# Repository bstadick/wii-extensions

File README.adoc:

= Wii Extension Controller Library for Arduino =

This project is an unofficial Arduino library for Wii extension controllers.

Use this library to receive data from your Wii extension controllers.

See examples folder for example usage with various Wii extension controllers.

See circuit folder for circuit board schematic to connect a Wii extension controller to an Arduino Nano.

See more information on the [Wii Brew Wiki](http://wiibrew.org/wiki/Wiimote/Extension_Controllers).

Project is based off of work by [Gabriel Bianconi](http://www.gabrielbianconi.com/)

Wii is a trademark of [Nintendo](https://www.nintendo.com/). The author of this library does not claim any ownership or association with Nintendo or their affiliates.

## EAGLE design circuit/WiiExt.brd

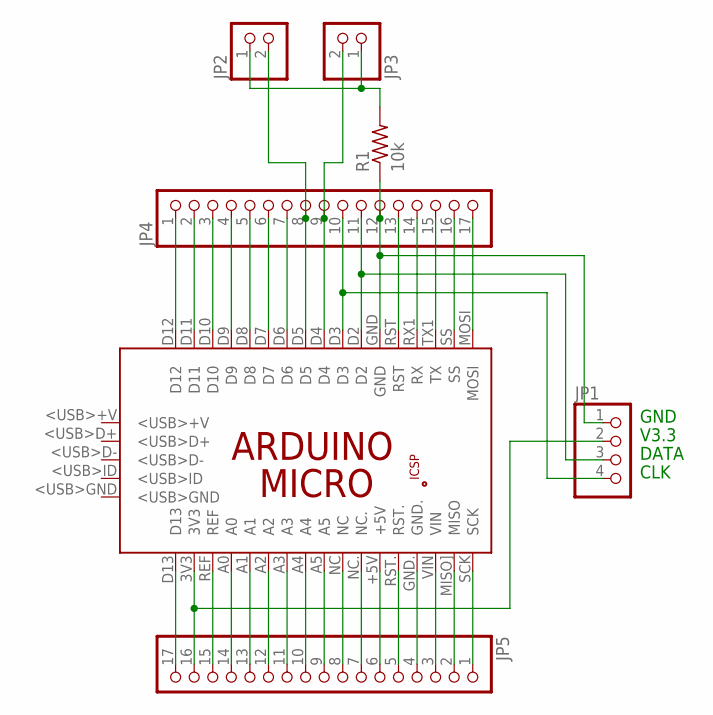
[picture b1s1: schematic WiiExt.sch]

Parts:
JP1: PINHD-1X4; 1X04
JP2, JP3: PINHD-1X2; 1X02
JP4, JP5: PINHD-1X17; 1X17
PCB1: ARDUINO_MICROOUTLINE; ARDUINO_MICRO
R1: 10k; 0204/7

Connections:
unnamed: JP1.4, JP4.10, PCB1.D3
unnamed: JP1.3, JP4.11, PCB1.D2
unnamed: JP1.1, JP4.12, PCB1.GND, R1.1
unnamed: JP1.2, JP5.16, PCB1.3V3
unnamed: JP4.1, PCB1.D12
unnamed: JP4.2, PCB1.D11
unnamed: JP4.3, PCB1.D10
unnamed: JP4.4, PCB1.D9
unnamed: JP4.5, PCB1.D8
unnamed: JP4.6, PCB1.D7
unnamed: JP4.7, PCB1.D6
unnamed: JP2.2, JP4.8, PCB1.D5
unnamed: JP3.2, JP4.9, PCB1.D4
unnamed: JP4.13, PCB1.RST
unnamed: JP4.14, PCB1.RX1 (RX)
unnamed: JP4.15, PCB1.TX1 (TX)
unnamed: JP4.16, PCB1.SS
unnamed: JP4.17, PCB1.MOSI
unnamed: JP5.17, PCB1.D13
unnamed: JP5.15, PCB1.REF
unnamed: JP5.14, PCB1.A0
unnamed: JP5.13, PCB1.A1
unnamed: JP5.12, PCB1.A2
unnamed: JP5.11, PCB1.A3
unnamed: JP5.10, PCB1.A4
unnamed: JP5.9, PCB1.A5
unnamed: JP5.8, PCB1.NC
unnamed: JP5.7, PCB1.NC.
unnamed: JP5.6, PCB1.+5V
unnamed: JP5.5, PCB1.RST.
unnamed: JP5.4, PCB1.GND.
unnamed: JP5.3, PCB1.VIN
unnamed: JP5.2, PCB1.MISO] (MISO)
unnamed: JP5.1, PCB1.SCK
unnamed: JP2.1, JP3.1, R1.2

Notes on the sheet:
GND
V3.3
DATA
CLK

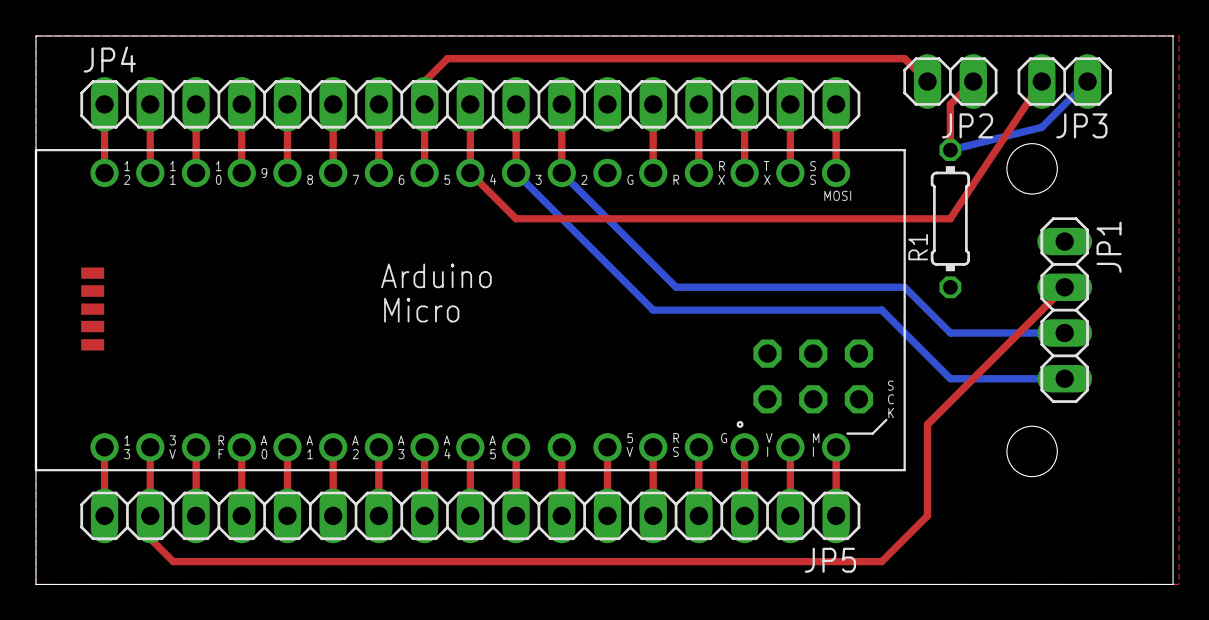
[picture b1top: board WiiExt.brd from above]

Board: 2 copper layers, 63.2 x 30.5 mm, 7 parts (0 on the bottom side), 35 nets.

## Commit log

2020-12-25 Added circuit and gitignore.
2020-12-25 Added Readme files.
2020-12-25 First commit of library, with taiko drum functionality.
2020-12-25 Updated with guitar hero guitar parsing. Added guitar hero guitar example.
2020-12-25 Updated gitignore to ignore temp eagle files.
2020-12-25 Updated library to work with guitar hero drum set. Updated/refractored demos. Added gh drum demo.
2020-12-25 Combine Readme files.
2020-12-25 Update license to MIT.
2020-12-27 Update license in each file to MIT.
2020-12-27 Update README with trademark information.
